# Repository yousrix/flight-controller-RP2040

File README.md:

# flight-controller-RP2040

drone flight controller based on RP2040

this project uses two boards.

the top board is a power distribution, dc-dc converter 3.3v, and current sensor

the bottom board is the main controller based on RP2040 and MPU-9250 sensor

specification

- 4 PWM
- 2 UART 
- 2 ADC
- 1 i2c
- 1 SPI

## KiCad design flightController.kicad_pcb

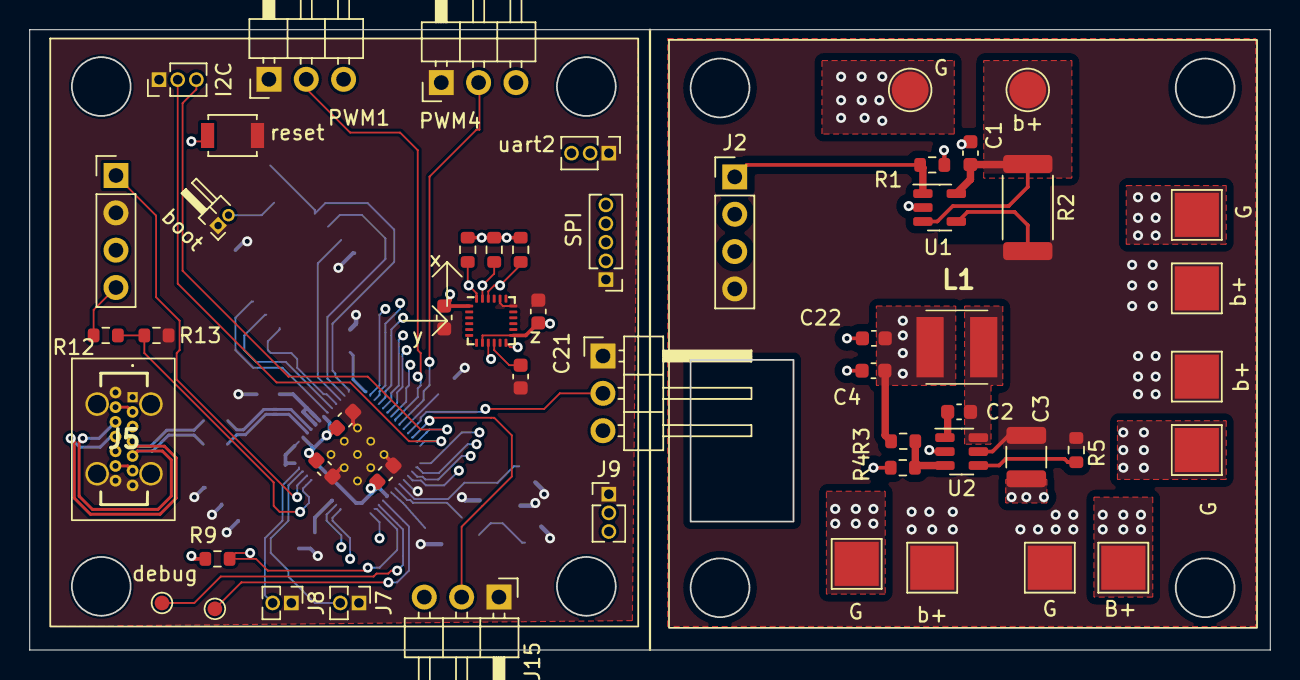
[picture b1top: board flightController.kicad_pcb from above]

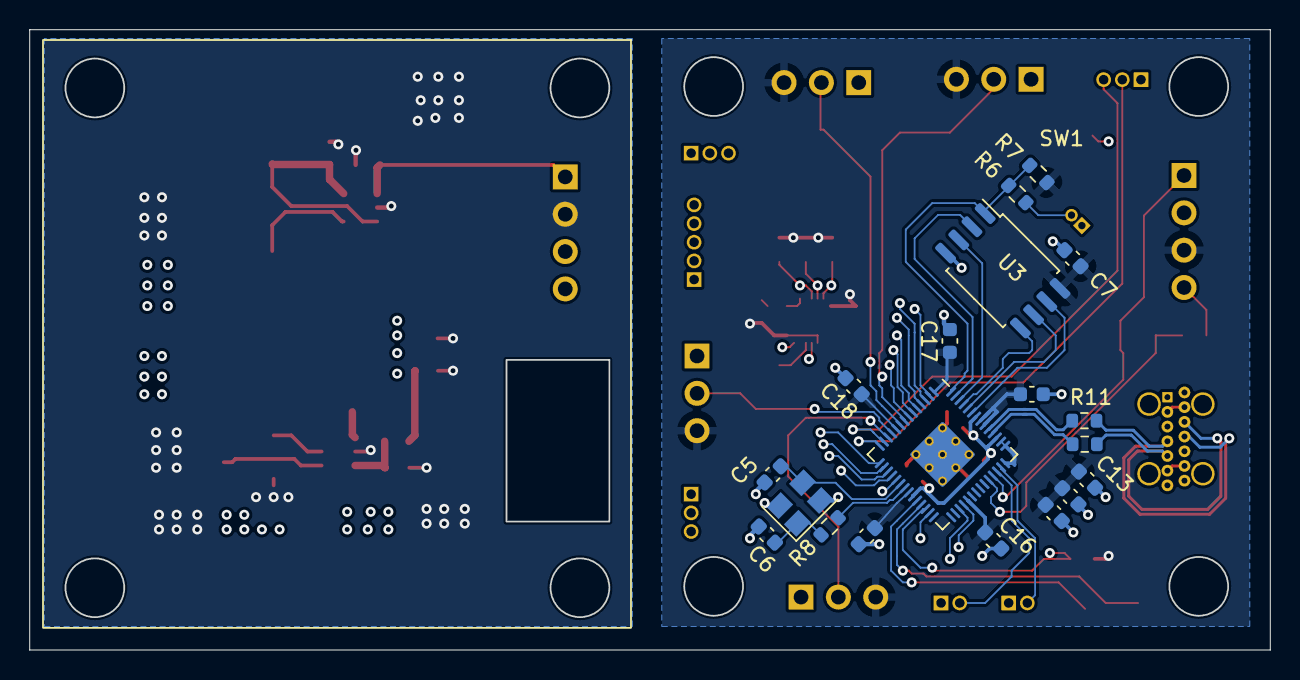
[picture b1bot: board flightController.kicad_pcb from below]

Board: 4 copper layers, 84.4 x 42.2 mm, 72 parts (19 on the bottom side), 53 nets.

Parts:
B+: esc3; TestPoint_Pad_3.0x3.0mm
C1, C20, C21, C22: 0.1uf; C_0603_1608Metric
C2, C7, C8, C9, C10, C11, C12, C13, C14, C15, C16, C17, C18, C19: 100nf; C_0603_1608Metric
C3: 10uf; C_1210_3225Metric
C4: 10uf; C_0603_1608Metric
C5, C6: 18pf; C_0603_1608Metric
G: esc1; TestPoint_Pad_3.0x3.0mm
G#2: esc3; TestPoint_Pad_3.0x3.0mm
G#3: esc2; TestPoint_Pad_3.0x3.0mm
G#4: esc4; TestPoint_Pad_3.0x3.0mm
J1: G; TestPoint_Pad_D2.5mm
J2: Con; pwrdisv1
J3: b+; TestPoint_Pad_D2.5mm
J4: boot; PinHeader_1x02_P1.00mm_Horizontal
J5: 918-468K2029E50000; 918468K2029E50000
J6: main; controllerV2
J7: ADC2; PinHeader_1x02_P1.27mm_Vertical
J8: ADC3; PinHeader_1x02_P1.27mm_Vertical
J9: uart1; PinHeader_1x03_P1.27mm_Vertical
J10: uart2; PinHeader_1x03_P1.27mm_Vertical
J11: I2C; PinHeader_1x03_P1.27mm_Vertical
J12: SPI; PinHeader_1x05_P1.27mm_Vertical
J13: PWM1; PinHeader_1x03_P2.54mm_Horizontal
J14: PWM2; PinHeader_1x03_P2.54mm_Horizontal
J15: PWM3; PinHeader_1x03_P2.54mm_Horizontal
J16: PWM4; PinHeader_1x03_P2.54mm_Horizontal
L1: 4.7uh; LQH5BPB100MT0L
R1: 1k; R_0603_1608Metric
R2: 0m50; R_2512_6332Metric
R3, R12: 20k; R_0603_1608Metric
R4: 4.5k; R_0603_1608Metric
R5: 100k; R_0603_1608Metric
R6, R7, R8, R9, R10, R11, R14, R15, R16: R; R_0603_1608Metric
R13: 5k; R_0603_1608Metric
SW1: reset; SW_SPST_B3U-1000P
U1: INA139; SOT-23-5
U2: ZTP7192YH; TSOT-23-6
U3: W25Q128JVS; SOIC-8_5.23x5.23mm_P1.27mm
U4: RP2040; RP2040-QFN-56
U5: MPU-9250; InvenSense_QFN-24_3x3mm_P0.4mm
Y1: Crystal_GND24; Crystal_SMD_3225-4Pin_3.2x2.5mm
b+: esc1; TestPoint_Pad_3.0x3.0mm
b+#2: esc2; TestPoint_Pad_3.0x3.0mm
b+#3: esc4; TestPoint_Pad_3.0x3.0mm
clk1: debug; TestPoint_Pad_D1.0mm
swd1: debug; TestPoint_Pad_D1.0mm

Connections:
3v3_distrub: C4.2, C22.2, J2.3, L1.2, R3.2
/mpu-9250/cs: R16.2, U4.16 (GPIO13), U5.22 (~CS)
/mpu-9250/intep: U4.27 (GPIO16), U5.12 (INT)
/mpu-9250/miso: U4.15 (GPIO12), U5.9 (AD0/MISO)
/mpu-9250/sck-slk: R15.2, U4.17 (GPIO14), U5.23 (SCL/SCLK)
/mpu-9250/sda-mosi: R14.2, U4.18 (GPIO15), U5.24 (SDA/MOSI)
/powerHub/sw: C2.2, L1.1, U2.6 (SW)
/rp2040/rp2040_1v1: C8.1, C9.1, C10.1, U4.23 (DVDD), U4.45 (VREG_VOUT), U4.50 (DVDD)
/rp2040/sd0: U3.5 (DI(IO0)), U4.53 (QSPI_SD0)
/rp2040/sd1: U3.2 (DO(IO1)), U4.55 (QSPI_SD1)
/rp2040/sd2: U3.3 (IO2), U4.54 (QSPI_SD2)
/rp2040/sd3: U3.7 (IO3), U4.51 (QSPI_SD3)
/rp2040/sd_clk: U3.6 (CLK), U4.52 (QSPI_SCLK)
/rp2040/sd_ss: R6.2, R7.2, U3.1 (~CS), U4.56 (QSPI_SS)
/rp2040/u+: R10.1, U4.47 (USB_DP)
/rp2040/u-: R11.1, U4.46 (USB_DM)
/rp2040/usb_boot: J4.2, R6.1
/rp2040/usb_d+: J5.A6 (DP1), J5.B6 (DP2), R10.2
/rp2040/usb_d-: J5.A7 (DN1), J5.B7 (DN2), R11.2
/rp2040/xin: C5.2, U4.20 (XIN), Y1.3
/rp2040/xout: R8.2, U4.21 (XOUT)
GND: B+.1, C1.2, C3.1, C4.1, C5.1, C6.1, C7.2, C8.2, C9.2, C10.2, C11.2, C12.2, C13.2, C14.2, C15.2, C16.2, C17.2, C18.2, C19.2, C20.2, C21.2, C22.1, G.1, G#3.1, G#4.1, J1.1, J2.2, J4.1, J5.A1 (GND_1), J5.A12 (GND_2), J5.B1 (GND_3), J5.B12 (GND_4), J5.MH1, J5.MH2, J5.MH3, J5.MH4, J6.2, J7.1, J8.1, J9.1, J10.1, J11.1, J12.1, J13.1, J14.1, J15.1, J16.1, R1.1, R4.1, R13.1, SW1.1, U1.2 (GND), U2.2 (GND), U3.4 (GND), U4.19 (TESTEN), U4.57 (GND), U5.18 (GND), U5.20 (RESV_GND), Y1.2, Y1.4
unnamed: C1.1, J3.1, R2.1, U1.3 (+), U1.5 (V+)
unnamed: C2.1, U2.1 (boot)
unnamed: C6.2, R8.1, Y1.1
unnamed: C21.1, U5.10 (REGOUT)
unnamed: J7.2, U4.40 (GPIO28_ADC2)
unnamed: J8.2, U4.41 (GPIO29_ADC3)
unnamed: J9.2, U4.32 (GPIO21)
unnamed: J9.3, U4.31 (GPIO20)
unnamed: J10.2, U4.3 (GPIO1)
unnamed: J10.3, U4.2 (GPIO0)
unnamed: J11.2, U4.14 (GPIO11)
unnamed: J11.3, U4.13 (GPIO10)
unnamed: J12.2, U4.7 (GPIO5)
unnamed: J12.3, U4.6 (GPIO4)
unnamed: J12.4, U4.5 (GPIO3)
unnamed: J12.5, U4.4 (GPIO2)
unnamed: J13.2, U4.8 (GPIO6)
unnamed: J14.2, U4.11 (GPIO8)
unnamed: J15.2, U4.12 (GPIO9)
unnamed: J16.2, U4.9 (GPIO7)
unnamed: R3.1, R4.2, U2.3 (FB)
unnamed: R5.1, U2.4 (EN)
unnamed: R9.2, SW1.2, U4.26 (RUN)
unnamed: R12.1, R13.2, U4.38 (GPIO26_ADC0)
unnamed: U4.24 (SWCLK), clk1.1
unnamed: U4.25 (SWD), swd1.1
crnt_distrub: J2.1, R1.2, U1.1
rp2040_3v3: C7.1, C11.1, C12.1, C13.1, C14.1, C15.1, C16.1, C17.1, C18.1, C19.1, C20.1, J6.3, J13.3, J14.3, J15.3, J16.3, R7.1, R9.1, R14.1, R15.1, R16.1, U3.8 (VCC), U4.1 (IOVDD), U4.10 (IOVDD), U4.22 (IOVDD), U4.33 (IOVDD), U4.42 (IOVDD), U4.43 (ADC_AVDD), U4.44 (VREG_IN), U4.48 (USB_VDD), U4.49 (IOVDD), U5.1 (RESV_VDDIO), U5.8 (VDDIO), U5.13 (VDD)
rp2040_crnt: J6.1, U4.39 (GPIO27_ADC1)
rp2040_vcc: J5.A4 (V_BUS_1), J5.A9 (V_BUS_2), J5.B4 (VBUS_1), J5.B9 (VBUS_2), J6.4, R12.2
vcc_distrub: C3.2, G#2.1, J2.4, R2.2, R5.2, U1.4 (-), U2.5 (IN), b+.1, b+#2.1, b+#3.1

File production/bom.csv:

Designator,Footprint,Quantity,Value,LCSC Part #
SW1,SW_SPST_B3U-1000P,1,reset,
J15,PinHeader_1x03_P2.54mm_Horizontal,1,PWM3,
clk1,TestPoint_Pad_D1.0mm,1,debug,
J11,PinHeader_1x03_P1.27mm_Vertical,1,I2C,
C2,C_0603_1608Metric,1,100nf,
R16,R_0603_1608Metric,1,R,
R12,R_0603_1608Metric,1,20k,
C8,C_0603_1608Metric,1,100nf,
R5,R_0603_1608Metric,1,100k,
J10,PinHeader_1x03_P1.27mm_Vertical,1,uart2,
G_4,TestPoint_Pad_3.0x3.0mm,1,esc1,
C9,C_0603_1608Metric,1,100nf,
R4,R_0603_1608Metric,1,4.5k,
J7,PinHeader_1x02_P1.27mm_Vertical,1,ADC2,
U2,TSOT-23-6,1,ZTP7192YH,
b+_3,TestPoint_Pad_3.0x3.0mm,1,esc1,
U5,InvenSense_QFN-24_3x3mm_P0.4mm,1,MPU-9250,
J8,PinHeader_1x02_P1.27mm_Vertical,1,ADC3,
C21,C_0603_1608Metric,1,0.1uf,
R15,R_0603_1608Metric,1,R,
C1,C_0603_1608Metric,1,0.1uf,
J9,PinHeader_1x03_P1.27mm_Vertical,1,uart1,
C19,C_0603_1608Metric,1,100nf,
b+_2,TestPoint_Pad_3.0x3.0mm,1,esc2,
U1,SOT-23-5,1,INA139,
R9,R_0603_1608Metric,1,R,
J3,TestPoint_Pad_D2.5mm,1,b+,
L1,LQH5BPB100MT0L,1,4.7uh,
C4,C_0603_1608Metric,1,10uf,
R1,R_0603_1608Metric,1,1k,
G_3,TestPoint_Pad_3.0x3.0mm,1,esc3,
J1,TestPoint_Pad_D2.5mm,1,G,
C22,C_0603_1608Metric,1,0.1uf,
J13,PinHeader_1x03_P2.54mm_Horizontal,1,PWM1,
C10,C_0603_1608Metric,1,100nf,
R13,R_0603_1608Metric,1,5k,
J16,PinHeader_1x03_P2.54mm_Horizontal,1,PWM4,
R3,R_0603_1608Metric,1,20k,
C20,C_0603_1608Metric,1,0.1uf,
b+,TestPoint_Pad_3.0x3.0mm,1,esc4,
J5,918468K2029E50000,1,918-468K2029E50000,
B+,TestPoint_Pad_3.0x3.0mm,1,esc3,
R14,R_0603_1608Metric,1,R,
G_2,TestPoint_Pad_3.0x3.0mm,1,esc2,
G,TestPoint_Pad_3.0x3.0mm,1,esc4,
J4,PinHeader_1x02_P1.00mm_Horizontal,1,boot,
J14,PinHeader_1x03_P2.54mm_Horizontal,1,PWM2,
J2,pwrdisv1,1,Con,
R2,R_2512_6332Metric,1,0m50,
J6,controllerV2,1,main,
swd1,TestPoint_Pad_D1.0mm,1,debug,
J12,PinHeader_1x05_P1.27mm_Vertical,1,SPI,
C3,C_1210_3225Metric,1,10uf,
R6,R_0603_1608Metric,1,R,
Y1,Crystal_SMD_3225-4Pin_3.2x2.5mm,1,Crystal_GND24,
C5,C_0603_1608Metric,1,18pf,
C15,C_0603_1608Metric,1,100nf,
U3,SOIC-8_5.23x5.23mm_P1.27mm,1,W25Q128JVS,
C6,C_0603_1608Metric,1,18pf,
C13,C_0603_1608Metric,1,100nf,
U4,RP2040-QFN-56,1,RP2040,
R8,R_0603_1608Metric,1,R,
C17,C_0603_1608Metric,1,100nf,
C18,C_0603_1608Metric,1,100nf,
R10,R_0603_1608Metric,1,R,
C12,C_0603_1608Metric,1,100nf,
C16,C_0603_1608Metric,1,100nf,
C11,C_0603_1608Metric,1,100nf,
C7,C_0603_1608Metric,1,100nf,
R7,R_0603_1608Metric,1,R,
C14,C_0603_1608Metric,1,100nf,
R11,R_0603_1608Metric,1,R,
